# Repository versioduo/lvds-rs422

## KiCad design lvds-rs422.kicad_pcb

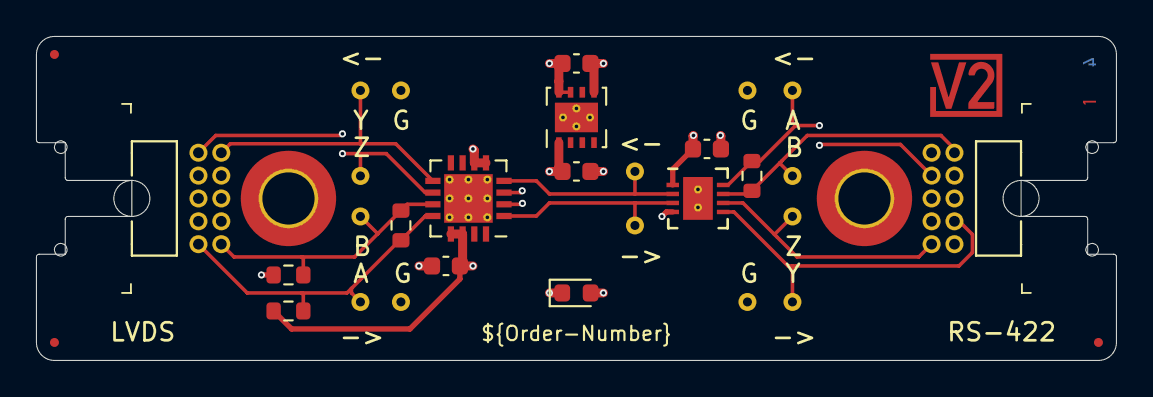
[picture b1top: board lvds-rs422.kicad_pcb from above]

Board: 4 copper layers, 60.0 x 18.0 mm, 38 parts (0 on the bottom side), 14 nets.

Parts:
C101, C102: 10u; C_0603_1608Metric
C1901, C2001: 0u1; C_0603_1608Metric
FID101, FID102, FID103: Fiducial; Fiducial_0.5mm_Mask1mm_Paste
ICON101: V2-logo; Logo_Small
INFO101: ORDER-NUMBER; Order_Number
INFO102: Layer_Numbers
J1901, J2001: 2x05_Horizontal; PinHeader_2x05_P1.27mm_Horizontal
PLUG101, PLUG102: PCB_Plug_Horizontal
R201, R202: 10k; R_0603_1608Metric
R1901, R2001: 120R; R_0603_1608Metric
SPACER101, SPACER102: 3mm; 9774030243
TP101, TP102, TP105, TP106, TP107, TP108, TP201, TP202, TP203, TP204, TP301, TP302, TP303, TP304: TestPoint_Small; TestPoint_THTPad_D1.0mm_Drill0.5mm
TVS101: CG0603MLC-05LE; D_0603_1608Metric
U102: TPS78433QWDRBRQ1; VSON-8-1_3x3mm_P0.65_EP1.65x2.4mm
U301: LTC2863; DFN-8-1EP_3x3mm_P0.5mm_EP1.65x2.38mm
U1902: SN65MLVD203B; WQFN-16-1EP_4x4mm_P0.65mm_EP2.7x2.7mm_ThermalVias

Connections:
+3V3: C102.1, C1901.1, C2001.1, R201.1, U102.1 (OUT), U301.1 (VCC), U1902.3 (DE), U1902.13 (VCC), U1902.14 (VCC)
+5V: C101.1, J1901.4, J1901.7, J2001.4, J2001.7, TVS101.2 (A), U102.7 (EN), U102.8 (IN)
/LVDS -> RS-422: TP102.1, U301.2 (RO), U1902.4 (D)
/Link Plug LVDS/RX-A: J1901.9, R201.2, R1901.1, TP201.1, U1902.12 (A)
/Link Plug LVDS/RX-B: J1901.10, R202.1, R1901.2, TP202.1, U1902.11 (B)
/Link Plug LVDS/TX-Y: J1901.2, TP204.1, U1902.9 (Y)
/Link Plug LVDS/TX-Z: J1901.1, TP203.1, U1902.10 (Z)
/Link Plug RS-422/RX-A: J2001.8, R2001.2, TP301.1, U301.8 (A)
/Link Plug RS-422/RX-B: J2001.9, R2001.1, TP302.1, U301.7 (B)
/Link Plug RS-422/TX-Y: J2001.3, TP304.1, U301.5 (Y)
/Link Plug RS-422/TX-Z: J2001.2, TP303.1, U301.6 (Z)
/RS-422 -> LVDS: TP101.1, U301.3 (DI), U1902.1 (R)
Earth: SPACER101.1, SPACER102.1
GND: C101.2, C102.2, C1901.2, C2001.2, J1901.3, J1901.8, J2001.1, J2001.10, R202.2, TP105.1, TP106.1, TP107.1, TP108.1, TVS101.1 (K), U102.5 (GND), U102.9 (GND), U301.4 (GND), U301.9 (GND), U1902.2 (RE), U1902.5 (GND), U1902.6 (GND), U1902.17 (GND)

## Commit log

2023-05-20 Import
2023-07-01 Refresh
2024-03-28 Update to Kicad 8
